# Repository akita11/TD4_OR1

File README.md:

# TD4_OR1

4bit CPU, TD4, in book ["How to Build CPU" ("CPUの創りかた" in Japanese)](https://www.amazon.co.jp/dp/4839909865/) using NDA-free PDK, [OpenRule1um](https://github.com/akita11/OpenRule1um).

## Contents

- Layout GDS: TD4core.GDS (open with [KLayout](https://www.klayout.de/), with [OpenRul1um PDK(https://github.com/MakeLSI/OpenRule1um) and [its standard cells](https://github.com/MakeLSI/OpenRule1um_StdCell) installed)

- Schematic: sch/TD4core.kicad_sch (open with EEschema in [KiCAD](https://www.kicad.org/))

## How to do LVS check

- Export netlit from TD4core.kicad_sch using EEschema, TD4core.cir.
- Add ".inc OR1SC.cir" at 2nd line in netlist file, TD4core.cir.
- Open TD4core.GDS with KLayout, execute "get_reference" macro with specifying TD4core.cir for reference netlist, and then, execute LVS (mainly digitl script).

## How to fabricate chip

- convert to fabrication GDS, with required information in fab's PDK, such as layer definitions, contact/via size conversion. Popular CMOS 0.6um PDK will satisfy OpenRule1um's design rule.

## Author

Junichi Akita (akita@fdi.jp), @akita11

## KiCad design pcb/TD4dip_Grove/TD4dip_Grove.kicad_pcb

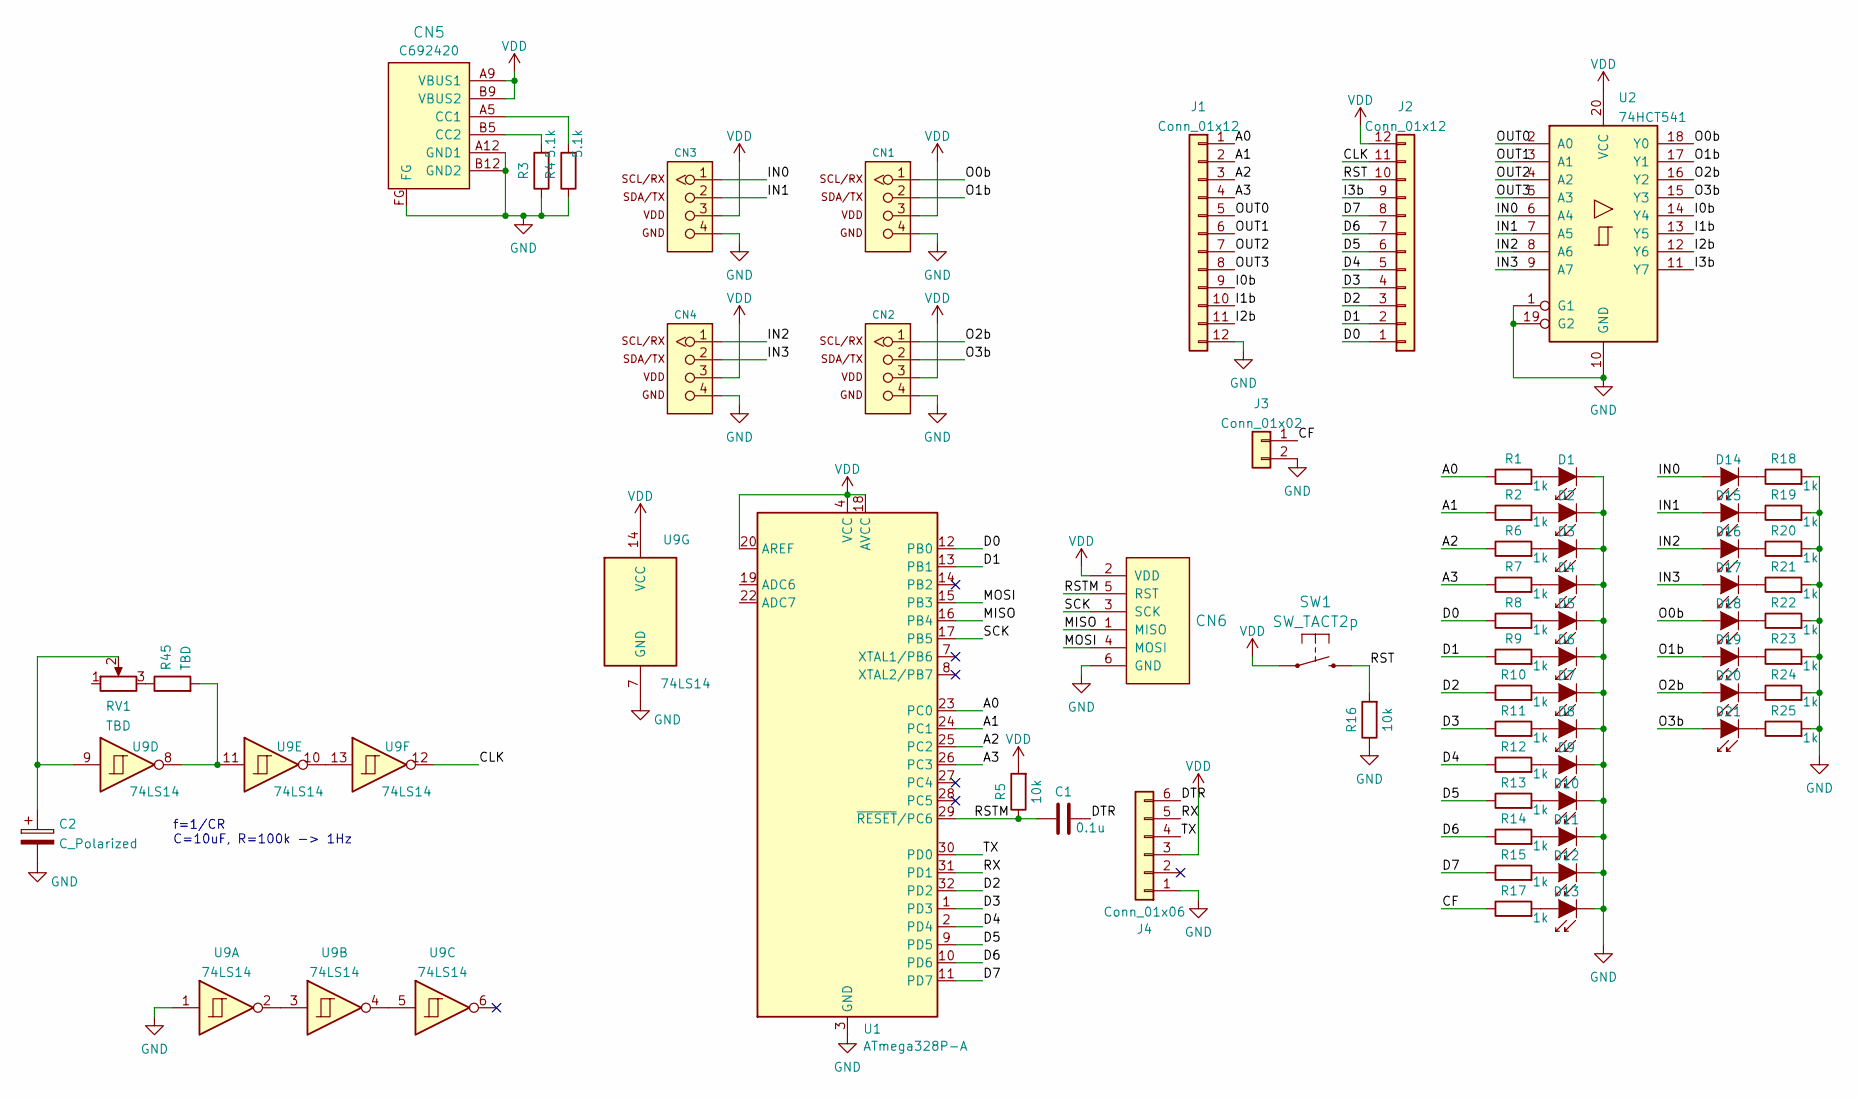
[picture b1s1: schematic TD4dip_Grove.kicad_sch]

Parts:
C1: 0.1u; C_0603_1608Metric
C2: C_Polarized; CP_Radial_D6.3mm_P2.50mm
CN1, CN2, CN3, CN4: CON_GROVE; CON_GROVE_H_roundPad
CN5: CON_USB-C-6; USB-C_6P; LCSC C692420
CN6: CON_AVRISP; PinSocket_2x03_P2.54mm_Vertical
D1, D2, D3, D4, D5, D6, D7, D8, D9, D10, D11, D12, D13, D14, D15, D16, D17, D18, D19, D20, D21: LED; LED_0603_1608Metric
J1, J2: Conn_01x12; PinSocket_1x12_P2.54mm_Vertical
J3: Conn_01x02; PinSocket_1x02_P2.54mm_Vertical
J4: Conn_01x06; PinHeader_1x06_P2.54mm_Horizontal
R1, R2, R6, R7, R8, R9, R10, R11, R12, R13, R14, R15, R17, R18, R19, R20, R21, R22, R23, R24, R25: 1k; R_0603_1608Metric
R3, R4: 5.1k; R_0603_1608Metric
R5, R16: 10k; R_0603_1608Metric
R45: TBD; R_0603_1608Metric
RV1: TBD; VR_POT_VR
SW1: SW_TACT2p; SW_Push_SPST_NO_Alps_SKRK
U1: ATmega328P-A; TQFP-32_7x7mm_P0.8mm
U2: 74HCT541; SSOP-20_4.4x6.5mm_P0.65mm
U9: 74LS14; SO-14_3.9x8.65mm_P1.27mm

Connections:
/A0: J1.1, R1.1, U1.23 (PC0)
/A1: J1.2, R2.1, U1.24 (PC1)
/A2: J1.3, R6.1, U1.25 (PC2)
/A3: J1.4, R7.1, U1.26 (PC3)
/CF: J3.1, R17.1
/CLK: J2.11, U9.12
/D0: J2.1, R8.1, U1.12 (PB0)
/D1: J2.2, R9.1, U1.13 (PB1)
/D2: J2.3, R10.1, U1.32 (PD2)
/D3: J2.4, R11.1, U1.1 (PD3)
/D4: J2.5, R12.1, U1.2 (PD4)
/D5: J2.6, R13.1, U1.9 (PD5)
/D6: J2.7, R14.1, U1.10 (PD6)
/D7: J2.8, R15.1, U1.11 (PD7)
/DTR: C1.2, J4.6
/I0b: J1.9, U2.14 (Y4)
/I1b: J1.10, U2.13 (Y5)
/I2b: J1.11, U2.12 (Y6)
/I3b: J2.9, U2.11 (Y7)
/IN0: CN3.1, D14.2 (A), U2.6 (A4)
/IN1: CN3.2, D15.2 (A), U2.7 (A5)
/IN2: CN4.1, D16.2 (A), U2.8 (A6)
/IN3: CN4.2, D17.2 (A), U2.9 (A7)
/MISO: CN6.1 (MISO), U1.16 (PB4)
/MOSI: CN6.4 (MOSI), U1.15 (PB3)
/O0b: CN1.1, D18.2 (A), U2.18 (Y0)
/O1b: CN1.2, D19.2 (A), U2.17 (Y1)
/O2b: CN2.1, D20.2 (A), U2.16 (Y2)
/O3b: CN2.2, D21.2 (A), U2.15 (Y3)
/OUT0: J1.5, U2.2 (A0)
/OUT1: J1.6, U2.3 (A1)
/OUT2: J1.7, U2.4 (A2)
/OUT3: J1.8, U2.5 (A3)
/RST: J2.10, R16.2, SW1.2
/RSTM: C1.1, CN6.5 (RST), R5.1, U1.29 (~RESET/PC6)
/RX: J4.5, U1.31 (PD1)
/SCK: CN6.3 (SCK), U1.17 (PB5)
/TX: J4.4, U1.30 (PD0)
GND: C2.2, CN1.4, CN2.4, CN3.4, CN4.4, CN5.A12 (GND1), CN5.B12 (GND2), CN5.FG, CN6.6 (GND), D1.1 (K), D2.1 (K), D3.1 (K), D4.1 (K), D5.1 (K), D6.1 (K), D7.1 (K), D8.1 (K), D9.1 (K), D10.1 (K), D11.1 (K), D12.1 (K), D13.1 (K), J1.12, J3.2, J4.1, R3.1, R4.1, R16.1, R18.2, R19.2, R20.2, R21.2, R22.2, R23.2, R24.2, R25.2, U1.3 (GND), U1.5 (GND), U1.21 (GND), U2.1 (G1), U2.10 (GND), U2.19 (G2), U9.1, U9.7 (GND)
unnamed: C2.1, RV1.2, U9.9
unnamed: CN5.A5 (CC1), R4.2
unnamed: CN5.B5 (CC2), R3.2
unnamed: D1.2 (A), R1.2
unnamed: D2.2 (A), R2.2
unnamed: D3.2 (A), R6.2
unnamed: D4.2 (A), R7.2
unnamed: D5.2 (A), R8.2
unnamed: D6.2 (A), R9.2
unnamed: D7.2 (A), R10.2
unnamed: D8.2 (A), R11.2
unnamed: D9.2 (A), R12.2
unnamed: D10.2 (A), R13.2
unnamed: D11.2 (A), R14.2
unnamed: D12.2 (A), R15.2
unnamed: D13.2 (A), R17.2
unnamed: D14.1 (K), R18.1
unnamed: D15.1 (K), R19.1
unnamed: D16.1 (K), R20.1
unnamed: D17.1 (K), R21.1
unnamed: D18.1 (K), R22.1
unnamed: D19.1 (K), R23.1
unnamed: D20.1 (K), R24.1
unnamed: D21.1 (K), R25.1
unnamed: R45.1, RV1.3
unnamed: R45.2, U9.8, U9.11
unnamed: U9.2, U9.3
unnamed: U9.4, U9.5
unnamed: U9.10, U9.13
VDD: CN1.3, CN2.3, CN3.3, CN4.3, CN5.A9 (VBUS1), CN5.B9 (VBUS2), CN6.2 (VDD), J2.12, J4.3, R5.2, SW1.1, U1.4 (VCC), U1.6 (VCC), U1.18 (AVCC), U1.20 (AREF), U2.20 (VCC), U9.14 (VCC)

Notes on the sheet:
f=1/CR C=10uF, R=100k -> 1Hz

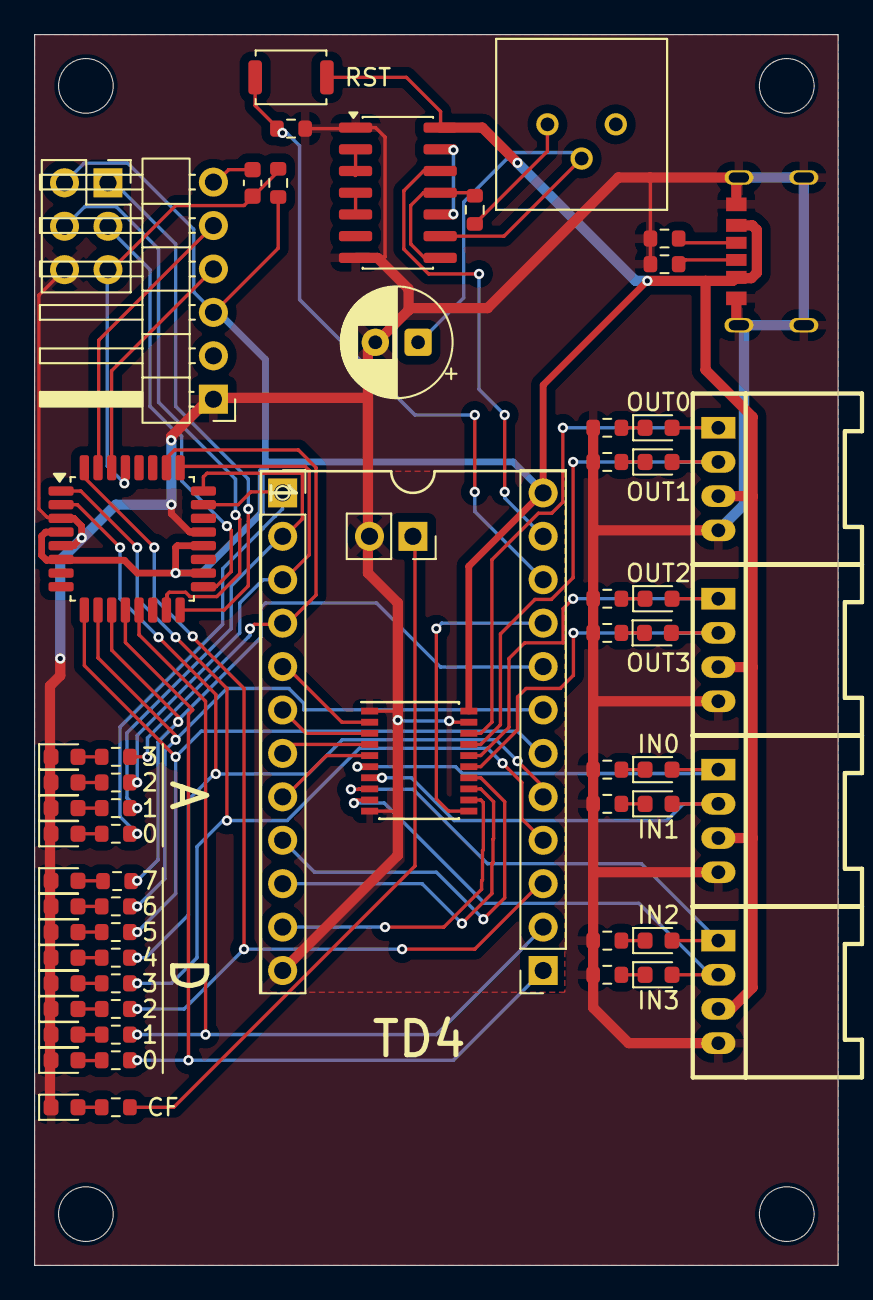
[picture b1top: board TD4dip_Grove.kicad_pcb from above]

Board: 2 copper layers, 47.0 x 72.0 mm, 64 parts (0 on the bottom side), 69 nets.

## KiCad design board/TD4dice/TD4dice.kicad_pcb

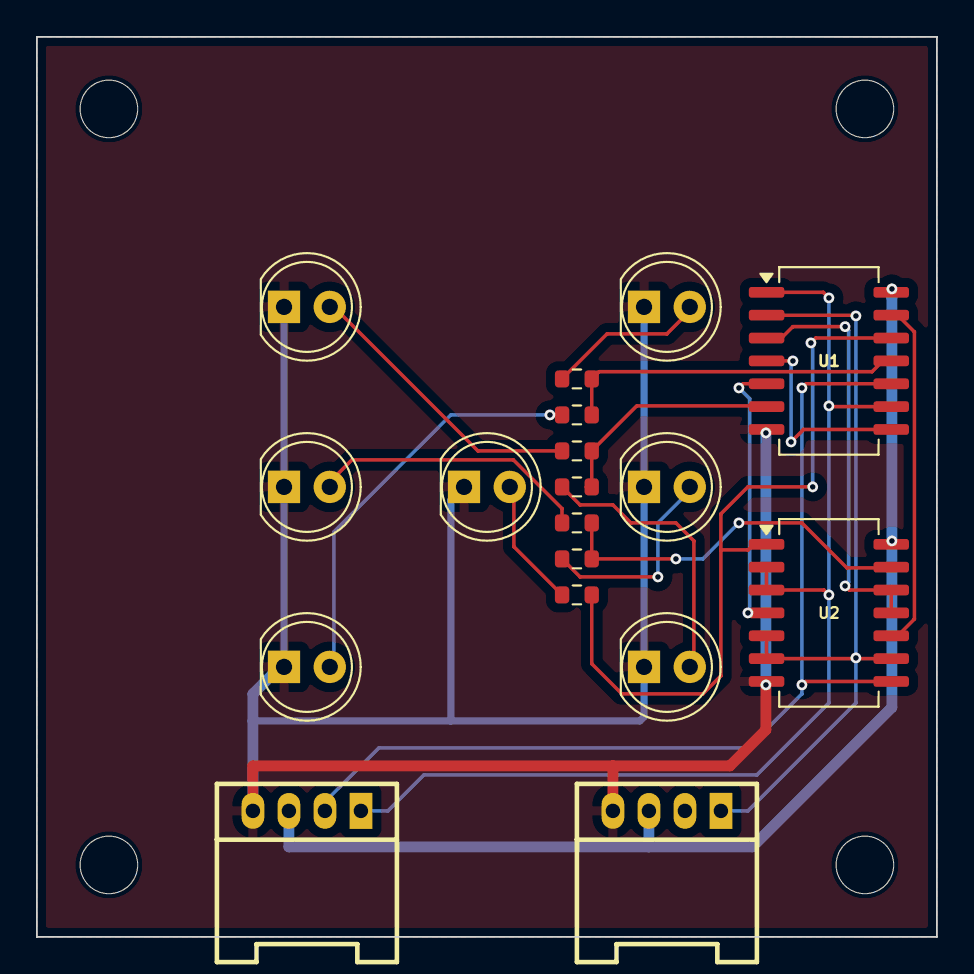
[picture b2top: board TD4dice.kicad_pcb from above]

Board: 2 copper layers, 50.0 x 50.0 mm, 18 parts (0 on the bottom side), 20 nets.

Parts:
CN1, CN2: CON_GROVE; CON_GROVE_H_roundPad
D1, D2, D3, D4, D5, D6, D7: LED; LED_D5.0mm
R1, R2, R3, R4, R5, R6, R7: 1k; R_0603_1608Metric
U1: 74HC00; SO-14_5.3x10.2mm_P1.27mm
U2: 7402; SO-14_5.3x10.2mm_P1.27mm

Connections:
+5V: CN1.3, CN2.3, U1.14 (VCC), U2.14 (VCC)
/A: CN1.1, U1.1, U1.9, U2.2, U2.3
/B: CN1.2, U1.10, U2.8
/C: CN2.1, U1.2, U2.5, U2.6, U2.9
/LEDAF: R1.1, R6.1, U1.6
/LEDBE: R2.1, R5.1, U1.11
/LEDCD: R3.1, R4.1, U2.13
/LEDG: R7.1, U1.12, U2.1
GND: CN1.4, CN2.4, D1.1 (K), D2.1 (K), D3.1 (K), D4.1 (K), D5.1 (K), D6.1 (K), D7.1 (K), U1.7 (GND), U2.7 (GND)
unnamed: D1.2 (A), R1.2
unnamed: D2.2 (A), R2.2
unnamed: D3.2 (A), R3.2
unnamed: D4.2 (A), R4.2
unnamed: D5.2 (A), R5.2
unnamed: D6.2 (A), R6.2
unnamed: D7.2 (A), R7.2
unnamed: U1.3, U2.11, U2.12
unnamed: U1.4, U1.8
unnamed: U1.5, U2.4
unnamed: U1.13, U2.10

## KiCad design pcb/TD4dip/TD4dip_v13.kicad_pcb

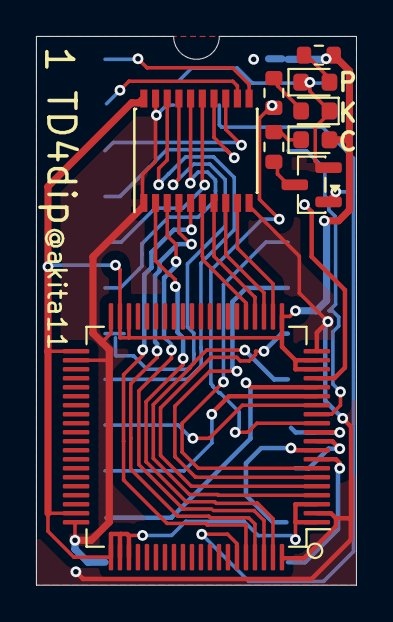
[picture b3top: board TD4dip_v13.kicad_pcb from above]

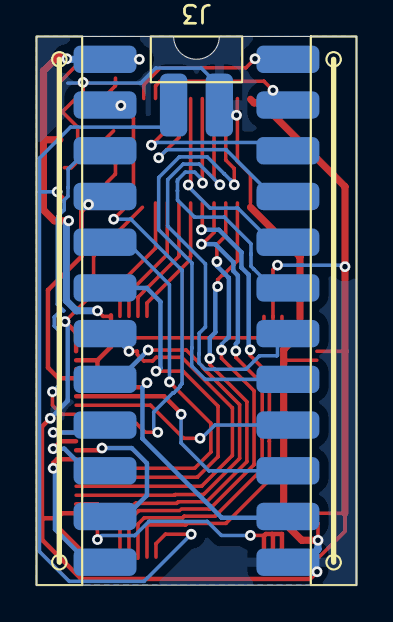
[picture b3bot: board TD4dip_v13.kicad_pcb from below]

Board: 2 copper layers, 17.8 x 30.5 mm, 12 parts (3 on the bottom side), 37 nets.

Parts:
D1, D2, D3: LED; LED_0603_1608Metric
J1, J2: Conn_01x12; CON_12pL_SMD
J3: Conn_01x02; CON_2pL_SMD
Q1: TR_NMOS_IRLML6344; SOT-23
R1, R2, R3: 1k; R_0603_1608Metric
U1: IC80p; LQFP-80_12x12mm_P0.5mm
U2: 74HCT541; SSOP-20_4.4x6.5mm_P0.65mm

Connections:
/A0: U1.22, U2.9 (A7)
/A0b: J1.1, U2.11 (Y7)
/A1: U1.23, U2.8 (A6)
/A1b: J1.2, U2.12 (Y6)
/A2: U1.24, U2.7 (A5)
/A2b: J1.3, U2.13 (Y5)
/A3: U1.25, U2.6 (A4)
/A3b: J1.4, U2.14 (Y4)
/CF: J3.1, Q1.1 (G), U1.75
/CLK: J2.11, R2.1, U1.12
/D0: J2.1, U1.8
/D1: J2.2, U1.9
/D2: J2.3, U1.10
/D3: J2.4, U1.11
/D4: J2.5, U1.4
/D5: J2.6, U1.5
/D6: J2.7, U1.6
/D7: J2.8, U1.7
/IN0: J1.9, U1.14
/IN1: J1.10, U1.15
/IN2: J1.11, U1.16
/IN3: J2.9, U1.17
/O0b: J1.5, U2.15 (Y3)
/O1b: J1.6, U2.16 (Y2)
/O2b: J1.7, U2.17 (Y1)
/O3b: J1.8, U2.18 (Y0)
/OUT0: U1.76, U2.5 (A3)
/OUT1: U1.77, U2.4 (A2)
/OUT2: U1.78, U2.3 (A1)
/OUT3: U1.79, U2.2 (A0)
/RST: J2.10, U1.13
GND: D1.1 (K), D2.1 (K), J1.12, J3.2, Q1.2 (S), U1.2, U1.20, U1.40, U1.42, U1.60, U1.80, U2.1 (G1), U2.10 (GND), U2.19 (G2)
unnamed: D1.2 (A), R1.2
unnamed: D2.2 (A), R2.2
unnamed: D3.1 (K), R3.2
unnamed: Q1.3 (D), R3.1
VDD: D3.2 (A), J2.12, R1.1, U1.1, U1.3, U1.18, U1.19, U1.21, U1.38, U1.39, U1.41, U1.59, U1.61, U1.62, U1.63, U2.20 (VCC)

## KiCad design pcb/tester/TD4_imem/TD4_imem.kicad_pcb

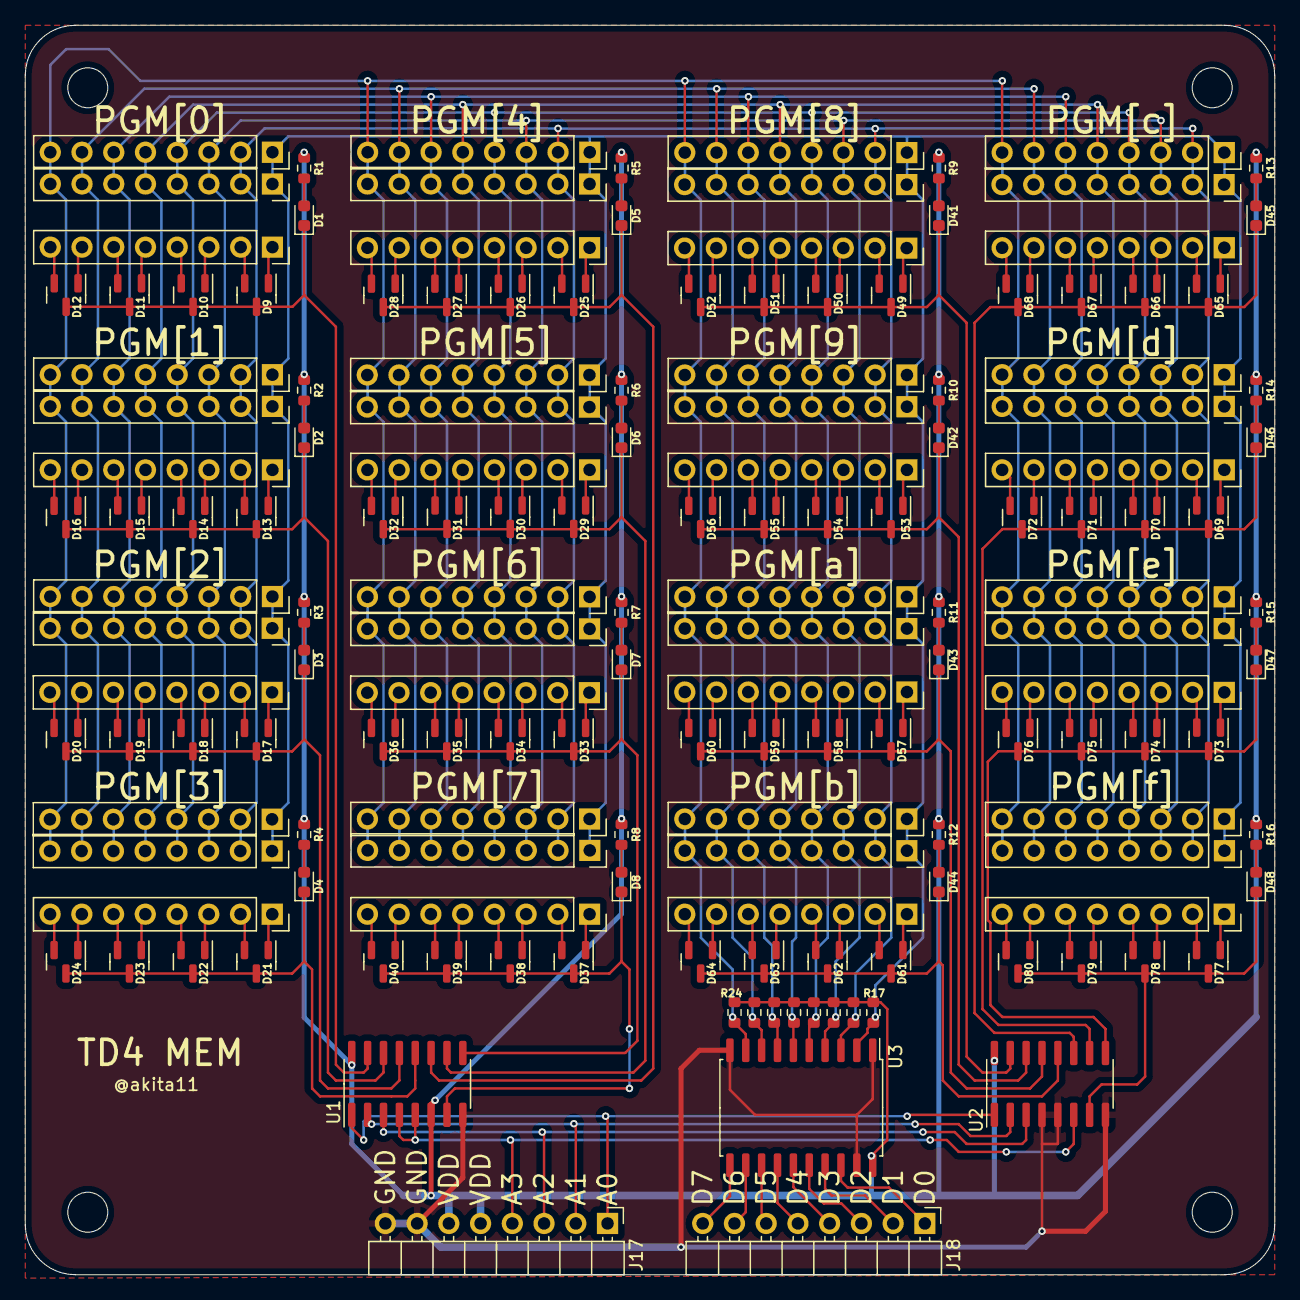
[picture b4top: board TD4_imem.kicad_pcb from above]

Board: 2 copper layers, 100.0 x 100.0 mm, 157 parts (0 on the bottom side), 182 nets.

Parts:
D1, D2, D3, D4, D5, D6, D7, D8, D41, D42, D43, D44, D45, D46, D47, D48: LED; LED_0603_1608Metric
D9, D10, D11, D12, D13, D14, D15, D16, D17, D18, D19, D20, D21, D22, D23, D24, D25, D26, D27, D28, D29, D30, D31, D32, D33, D34, D35, D36, D37, D38, D39, D40, D49, D50, D51, D52, D53, D54, D55, D56, D57, D58, D59, D60, D61, D62, D63, D64, D65, D66, D67, D68, D69, D70, D71, D72, D73, D74, D75, D76, D77, D78, D79, D80: BAT54C; SOT-23
J1, J2, J3, J4, J5, J6, J7, J8, J9, J10, J11, J12, J13, J14, J15, J16, J101, J102, J103, J104, J105, J106, J107, J108, J109, J110, J111, J112, J113, J114, J115, J116, J201, J202, J203, J204, J205, J206, J207, J208, J209, J210, J211, J212, J213, J214, J215, J216: Conn_01x08; PinSocket_1x08_P2.54mm_Vertical
J17, J18: Conn_01x08; PinHeader_1x08_P2.54mm_Horizontal
R1, R2, R3, R4, R5, R6, R7, R8, R9, R10, R11, R12, R13, R14, R15, R16: 1k; R_0603_1608Metric
R17, R18, R19, R20, R21, R22, R23, R24: 10k; R_0603_1608Metric
U1, U2: 74LS138; SOIC-16_3.9x9.9mm_P1.27mm
U3: 74LS540; SOP-20_7.5x12.8mm_P1.27mm

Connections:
/A0: J17.1, U1.1 (A0), U2.1 (A0)
/A1: J17.2, U1.2 (A1), U2.2 (A1)
/A2: J17.3, U1.3 (A2), U2.3 (A2)
/A3: J17.4, U1.4 (E1), U1.5 (E2), U2.6 (E3)
/D0: J1.1, J2.1, J3.1, J4.1, J5.1, J6.1, J7.1, J8.1, J9.1, J10.1, J11.1, J12.1, J13.1, J14.1, J15.1, J16.1, J101.1, J102.1, J103.1, J104.1, J105.1, J106.1, J107.1, J108.1, J109.1, J110.1, J111.1, J112.1, J113.1, J114.1, J115.1, J116.1, R17.2, U3.2 (A0)
/D1: J1.2, J2.2, J3.2, J4.2, J5.2, J6.2, J7.2, J8.2, J9.2, J10.2, J11.2, J12.2, J13.2, J14.2, J15.2, J16.2, J101.2, J102.2, J103.2, J104.2, J105.2, J106.2, J107.2, J108.2, J109.2, J110.2, J111.2, J112.2, J113.2, J114.2, J115.2, J116.2, R18.2, U3.3 (A1)
/D2: J1.3, J2.3, J3.3, J4.3, J5.3, J6.3, J7.3, J8.3, J9.3, J10.3, J11.3, J12.3, J13.3, J14.3, J15.3, J16.3, J101.3, J102.3, J103.3, J104.3, J105.3, J106.3, J107.3, J108.3, J109.3, J110.3, J111.3, J112.3, J113.3, J114.3, J115.3, J116.3, R19.2, U3.4 (A2)
/D3: J1.4, J2.4, J3.4, J4.4, J5.4, J6.4, J7.4, J8.4, J9.4, J10.4, J11.4, J12.4, J13.4, J14.4, J15.4, J16.4, J101.4, J102.4, J103.4, J104.4, J105.4, J106.4, J107.4, J108.4, J109.4, J110.4, J111.4, J112.4, J113.4, J114.4, J115.4, J116.4, R20.2, U3.5 (A3)
/D4: J1.5, J2.5, J3.5, J4.5, J5.5, J6.5, J7.5, J8.5, J9.5, J10.5, J11.5, J12.5, J13.5, J14.5, J15.5, J16.5, J101.5, J102.5, J103.5, J104.5, J105.5, J106.5, J107.5, J108.5, J109.5, J110.5, J111.5, J112.5, J113.5, J114.5, J115.5, J116.5, R21.2, U3.6 (A4)
/D5: J1.6, J2.6, J3.6, J4.6, J5.6, J6.6, J7.6, J8.6, J9.6, J10.6, J11.6, J12.6, J13.6, J14.6, J15.6, J16.6, J101.6, J102.6, J103.6, J104.6, J105.6, J106.6, J107.6, J108.6, J109.6, J110.6, J111.6, J112.6, J113.6, J114.6, J115.6, J116.6, R22.2, U3.7 (A5)
/D6: J1.7, J2.7, J3.7, J4.7, J5.7, J6.7, J7.7, J8.7, J9.7, J10.7, J11.7, J12.7, J13.7, J14.7, J15.7, J16.7, J101.7, J102.7, J103.7, J104.7, J105.7, J106.7, J107.7, J108.7, J109.7, J110.7, J111.7, J112.7, J113.7, J114.7, J115.7, J116.7, R23.2, U3.8 (A6)
/D7: J1.8, J2.8, J3.8, J4.8, J5.8, J6.8, J7.8, J8.8, J9.8, J10.8, J11.8, J12.8, J13.8, J14.8, J15.8, J16.8, J101.8, J102.8, J103.8, J104.8, J105.8, J106.8, J107.8, J108.8, J109.8, J110.8, J111.8, J112.8, J113.8, J114.8, J115.8, J116.8, R24.2, U3.9 (A7)
/DB0: J18.1, U3.18 (Y0)
/DB1: J18.2, U3.17 (Y1)
/DB2: J18.3, U3.16 (Y2)
/DB3: J18.4, U3.15 (Y3)
/DB4: J18.5, U3.14 (Y4)
/DB5: J18.6, U3.13 (Y5)
/DB6: J18.7, U3.12 (Y6)
/DB7: J18.8, U3.11 (Y7)
GND: J17.7, J17.8, U1.8 (GND), U2.4 (E1), U2.5 (E2), U2.8 (GND), U3.1 (G1), U3.10 (GND), U3.19 (G2)
unnamed: D1.1 (K), D9.3, D10.3, D11.3, D12.3, U1.15 (O0)
unnamed: D1.2 (A), R1.2
unnamed: D2.2 (A), R2.2
unnamed: D3.2 (A), R3.2
unnamed: D4.2 (A), R4.2
unnamed: D5.2 (A), R5.2
unnamed: D6.2 (A), R6.2
unnamed: D7.2 (A), R7.2
unnamed: D8.2 (A), R8.2
unnamed: D9.1, J201.1
unnamed: D9.2, J201.2
unnamed: D10.1, J201.3
unnamed: D10.2, J201.4
unnamed: D11.1, J201.5
unnamed: D11.2, J201.6
unnamed: D12.1, J201.7
unnamed: D12.2, J201.8
unnamed: D13.1, J202.1
unnamed: D13.2, J202.2
unnamed: D2.1 (K), D13.3, D14.3, D15.3, D16.3, U1.14 (O1)
unnamed: D14.1, J202.3
unnamed: D14.2, J202.4
unnamed: D15.1, J202.5
unnamed: D15.2, J202.6
unnamed: D16.1, J202.7
unnamed: D16.2, J202.8
unnamed: D17.1, J203.1
unnamed: D17.2, J203.2
unnamed: D3.1 (K), D17.3, D18.3, D19.3, D20.3, U1.13 (O2)
unnamed: D18.1, J203.3
unnamed: D18.2, J203.4
unnamed: D19.1, J203.5
unnamed: D19.2, J203.6
unnamed: D20.1, J203.7
unnamed: D20.2, J203.8
unnamed: D21.1, J204.1
unnamed: D21.2, J204.2
unnamed: D4.1 (K), D21.3, D22.3, D23.3, D24.3, U1.12 (O3)
unnamed: D22.1, J204.3
unnamed: D22.2, J204.4
unnamed: D23.1, J204.5
unnamed: D23.2, J204.6
unnamed: D24.1, J204.7
unnamed: D24.2, J204.8
unnamed: D25.1, J205.1
unnamed: D25.2, J205.2
unnamed: D5.1 (K), D25.3, D26.3, D27.3, D28.3, U1.11 (O4)
unnamed: D26.1, J205.3
unnamed: D26.2, J205.4
unnamed: D27.1, J205.5
unnamed: D27.2, J205.6
unnamed: D28.1, J205.7
unnamed: D28.2, J205.8
unnamed: D29.1, J206.1
unnamed: D29.2, J206.2
unnamed: D6.1 (K), D29.3, D30.3, D31.3, D32.3, U1.10 (O5)
unnamed: D30.1, J206.3
unnamed: D30.2, J206.4
unnamed: D31.1, J206.5
unnamed: D31.2, J206.6
unnamed: D32.1, J206.7
unnamed: D32.2, J206.8
unnamed: D33.1, J207.1
unnamed: D33.2, J207.2
unnamed: D7.1 (K), D33.3, D34.3, D35.3, D36.3, U1.9 (O6)
unnamed: D34.1, J207.3
unnamed: D34.2, J207.4
unnamed: D35.1, J207.5
unnamed: D35.2, J207.6
unnamed: D36.1, J207.7
unnamed: D36.2, J207.8
unnamed: D37.1, J208.1
unnamed: D37.2, J208.2
unnamed: D8.1 (K), D37.3, D38.3, D39.3, D40.3, U1.7 (O7)
unnamed: D38.1, J208.3
unnamed: D38.2, J208.4
unnamed: D39.1, J208.5
unnamed: D39.2, J208.6
unnamed: D40.1, J208.7
unnamed: D40.2, J208.8
unnamed: D41.1 (K), D49.3, D50.3, D51.3, D52.3, U2.15 (O0)
unnamed: D41.2 (A), R9.2
unnamed: D42.1 (K), D53.3, D54.3, D55.3, D56.3, U2.14 (O1)
unnamed: D42.2 (A), R10.2
unnamed: D43.1 (K), D57.3, D58.3, D59.3, D60.3, U2.13 (O2)
unnamed: D43.2 (A), R11.2
unnamed: D44.1 (K), D61.3, D62.3, D63.3, D64.3, U2.12 (O3)
unnamed: D44.2 (A), R12.2
unnamed: D45.1 (K), D65.3, D66.3, D67.3, D68.3, U2.11 (O4)
unnamed: D45.2 (A), R13.2
unnamed: D46.1 (K), D69.3, D70.3, D71.3, D72.3, U2.10 (O5)
unnamed: D46.2 (A), R14.2
unnamed: D47.1 (K), D73.3, D74.3, D75.3, D76.3, U2.9 (O6)
unnamed: D47.2 (A), R15.2
unnamed: D48.1 (K), D77.3, D78.3, D79.3, D80.3, U2.7 (O7)
unnamed: D48.2 (A), R16.2
unnamed: D49.1, J209.1
unnamed: D49.2, J209.2
unnamed: D50.1, J209.3
unnamed: D50.2, J209.4
unnamed: D51.1, J209.5
unnamed: D51.2, J209.6
unnamed: D52.1, J209.7
unnamed: D52.2, J209.8
unnamed: D53.1, J210.1
unnamed: D53.2, J210.2
unnamed: D54.1, J210.3
unnamed: D54.2, J210.4
unnamed: D55.1, J210.5
unnamed: D55.2, J210.6
unnamed: D56.1, J210.7
unnamed: D56.2, J210.8
unnamed: D57.1, J211.1
unnamed: D57.2, J211.2
unnamed: D58.1, J211.3
unnamed: D58.2, J211.4
unnamed: D59.1, J211.5
unnamed: D59.2, J211.6
unnamed: D60.1, J211.7
unnamed: D60.2, J211.8
unnamed: D61.1, J212.1
unnamed: D61.2, J212.2
unnamed: D62.1, J212.3
unnamed: D62.2, J212.4
unnamed: D63.1, J212.5
unnamed: D63.2, J212.6
unnamed: D64.1, J212.7
unnamed: D64.2, J212.8
unnamed: D65.1, J213.1
unnamed: D65.2, J213.2
unnamed: D66.1, J213.3
unnamed: D66.2, J213.4
unnamed: D67.1, J213.5
unnamed: D67.2, J213.6
unnamed: D68.1, J213.7
unnamed: D68.2, J213.8
unnamed: D69.1, J214.1
unnamed: D69.2, J214.2
unnamed: D70.1, J214.3
unnamed: D70.2, J214.4
unnamed: D71.1, J214.5
unnamed: D71.2, J214.6
unnamed: D72.1, J214.7
unnamed: D72.2, J214.8
unnamed: D73.1, J215.1
unnamed: D73.2, J215.2
unnamed: D74.1, J215.3
unnamed: D74.2, J215.4
unnamed: D75.1, J215.5
unnamed: D75.2, J215.6
unnamed: D76.1, J215.7
unnamed: D76.2, J215.8
unnamed: D77.1, J216.1
unnamed: D77.2, J216.2
unnamed: D78.1, J216.3
unnamed: D78.2, J216.4
unnamed: D79.1, J216.5
unnamed: D79.2, J216.6
unnamed: D80.1, J216.7
unnamed: D80.2, J216.8
VDD: J17.5, J17.6, R1.1, R2.1, R3.1, R4.1, R5.1, R6.1, R7.1, R8.1, R9.1, R10.1, R11.1, R12.1, R13.1, R14.1, R15.1, R16.1, R17.1, R18.1, R19.1, R20.1, R21.1, R22.1, R23.1, R24.1, U1.6 (E3), U1.16 (VCC), U2.16 (VCC), U3.20 (VCC)

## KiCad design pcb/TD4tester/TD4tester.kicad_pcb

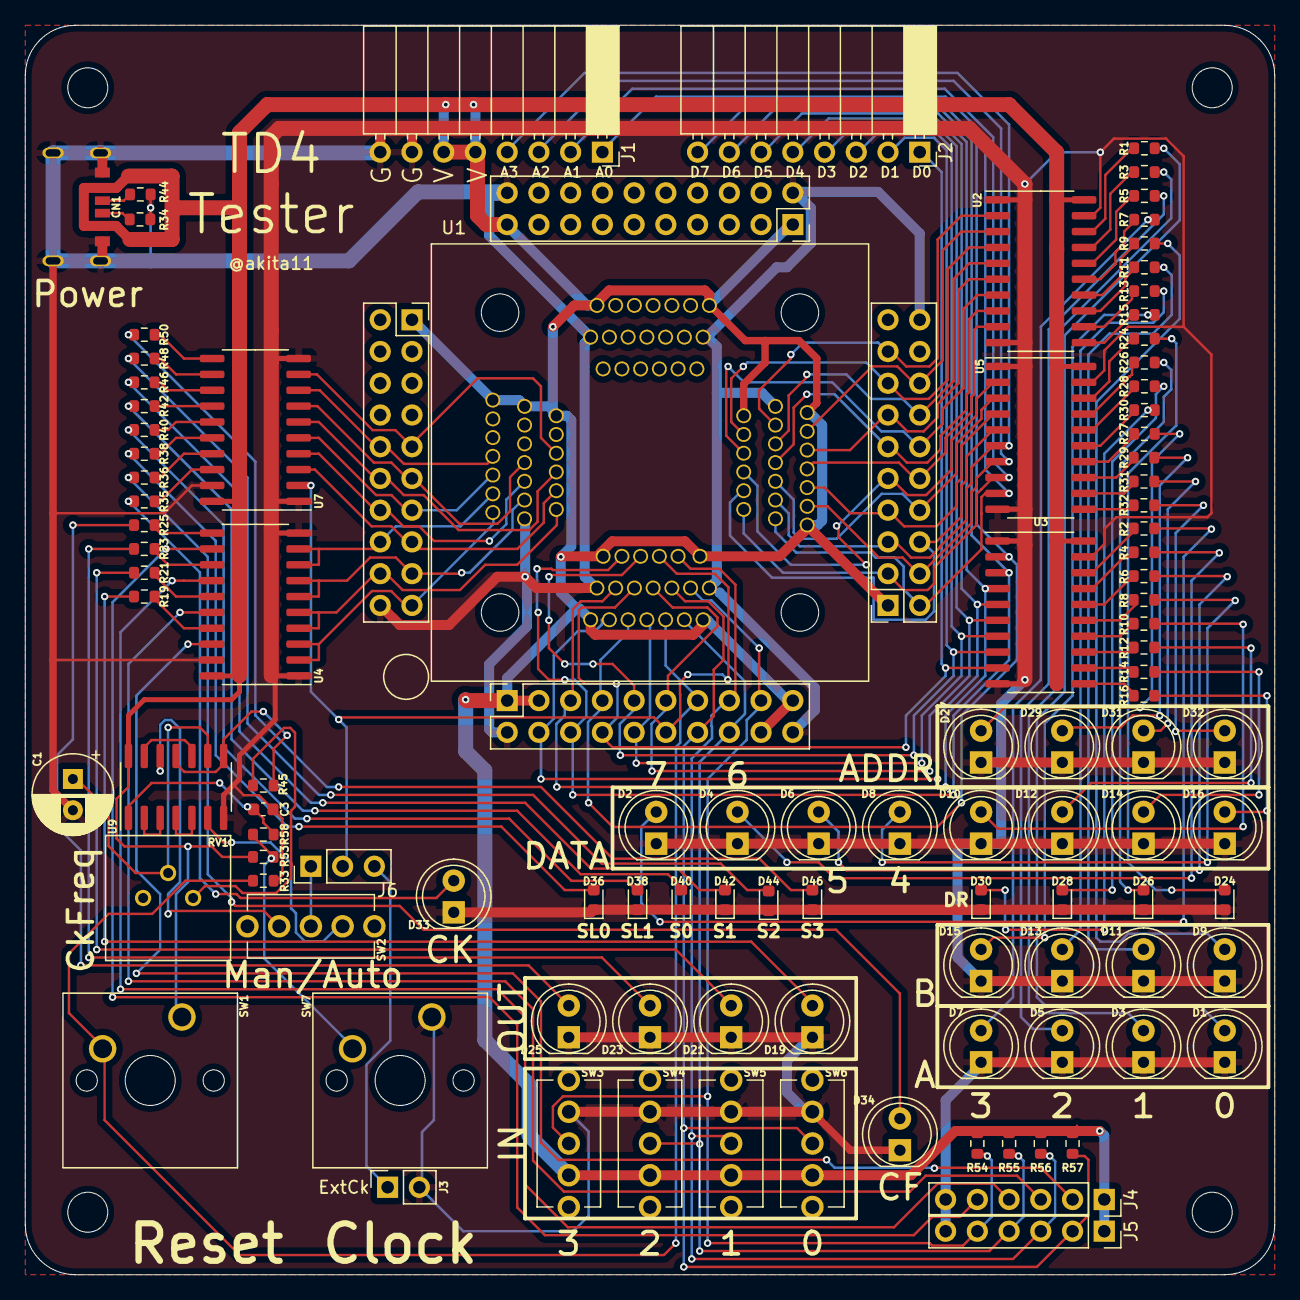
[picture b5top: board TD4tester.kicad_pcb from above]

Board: 2 copper layers, 100.0 x 100.0 mm, 110 parts (0 on the bottom side), 133 nets.

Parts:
C1: C_Polarized; CP_Radial_D6.3mm_P2.50mm
C3: C; C_0603_1608Metric
CN1: CON_USB-C-6; USB-C_6P
D1, D2, D3, D4, D5, D6, D7, D8, D9, D10, D11, D12, D13, D14, D15, D16, D19, D21, D23, D25, D27, D29, D31, D32, D33, D34: LED; LED_D5.0mm
D24, D26, D28, D30, D36, D38, D40, D42, D44, D46: LED; LED_0603_1608Metric
J1, J2: Conn_01x08; PinSocket_1x08_P2.54mm_Horizontal
J3: Conn_01x02; PinSocket_1x02_P2.54mm_Vertical
J4, J5: Conn_01x06; PinSocket_1x06_P2.54mm_Vertical
J6: Conn_01x03; PinHeader_1x03_P2.54mm_Vertical
J7, J8, J9, J10: Conn_02x10_Odd_Even; PinSocket_2x10_P2.54mm_Vertical
R1, R2, R3, R4, R5, R6, R7, R8, R9, R10, R11, R12, R13, R14, R15, R16, R19, R21, R23, R24, R25, R26, R27, R28, R29, R30, R31, R32, R35, R36, R38, R40, R42, R46, R48, R50: 1k; R_0603_1608Metric
R33, R53, R54, R55, R56, R57, R58: 10k; R_0603_1608Metric
R34, R44: 5.1k; R_0603_1608Metric
R45: TBD; R_0603_1608Metric
RV1: TBD; VR_POT_VR
SW1, SW7: SW_Push; SW_Cherry_MX_1.00u_PCB
SW2, SW3, SW4, SW5, SW6: SW_SPDT; SW_SPDT_Frame
U1: IC80p; SOCKET_IC51-0804-808
U2, U3, U4, U5, U7: 74LS541; SO-20_5.3x12.6mm_P1.27mm
U9: 74LS14; SO-14_3.9x8.65mm_P1.27mm

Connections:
/A0: J1.1, J8.2, U1.22, U5.9 (A7)
/A1: J1.2, J8.3, U1.23, U5.8 (A6)
/A2: J1.3, J8.4, U1.24, U5.7 (A5)
/A3: J1.4, J8.5, U1.25, U5.6 (A4)
/CF: J10.15, U1.75, U7.3 (A1)
/CK: J6.2, J7.12, U1.12, U7.2 (A0)
/CKe: J3.1, J6.3
/D0: J2.1, J7.8, U1.8, U3.9 (A7)
/D1: J2.2, J7.9, U1.9, U3.8 (A6)
/D2: J2.3, J7.10, U1.10, U3.7 (A5)
/D3: J2.4, J7.11, U1.11, U3.6 (A4)
/D4: J2.5, J7.4, U1.4, U3.5 (A3)
/D5: J2.6, J7.5, U1.5, U3.4 (A2)
/D6: J2.7, J7.6, U1.6, U3.3 (A1)
/D7: J2.8, J7.7, U1.7, U3.2 (A0)
/DA0: J8.17, U1.37, U2.2 (A0)
/DA1: J8.16, U1.36, U2.3 (A1)
/DA2: J8.15, U1.35, U2.4 (A2)
/DA3: J8.14, U1.34, U2.5 (A3)
/DB0: J8.13, U1.33, U2.6 (A4)
/DB1: J8.12, U1.32, U2.7 (A5)
/DB2: J8.11, U1.31, U2.8 (A6)
/DB3: J8.10, U1.30, U2.9 (A7)
/DR0: J8.9, U1.29, U5.2 (A0)
/DR1: J8.8, U1.28, U5.3 (A1)
/DR2: J8.7, U1.27, U5.4 (A2)
/DR3: J8.6, U1.26, U5.5 (A3)
/IN0: J5.2, J7.14, R57.2, SW6.2 (B), U1.14
/IN1: J5.3, J7.15, R56.2, SW5.2 (B), U1.15
/IN2: J5.4, J7.16, R55.2, SW4.2 (B), U1.16
/IN3: J5.5, J7.17, R54.2, SW3.2 (B), U1.17
/OUT0: J10.16, U1.76, U4.8 (A6), U4.9 (A7)
/OUT0e: J4.2, U4.18 (Y0)
/OUT1: J10.17, U1.77, U4.6 (A4), U4.7 (A5)
/OUT1e: J4.3, U4.16 (Y2)
/OUT2: J10.18, U1.78, U4.4 (A2), U4.5 (A3)
/OUT2e: J4.4, U4.14 (Y4)
/OUT3: J10.19, U1.79, U4.2 (A0), U4.3 (A1)
/OUT3e: J4.5, U4.12 (Y6)
/RST: J7.13, R33.1, SW1.2, U1.13
/S0: J10.12, U1.72, U7.6 (A4)
/S1: J10.11, U1.71, U7.7 (A5)
/S2: J10.10, U1.70, U7.8 (A6)
/S3: J10.9, U1.69, U7.9 (A7)
/SL0: J10.14, U1.74, U7.4 (A2)
/SL1: J10.13, U1.73, U7.5 (A3)
GND: C1.2, C3.2, CN1.A12 (GND1), CN1.B12 (GND2), CN1.FG, D1.1 (K), D2.1 (K), D3.1 (K), D4.1 (K), D5.1 (K), D6.1 (K), D7.1 (K), D8.1 (K), D9.1 (K), D10.1 (K), D11.1 (K), D12.1 (K), D13.1 (K), D14.1 (K), D15.1 (K), D16.1 (K), D19.1 (K), D21.1 (K), D23.1 (K), D24.1 (K), D25.1 (K), D26.1 (K), D27.1 (K), D28.1 (K), D29.1 (K), D30.1 (K), D31.1 (K), D32.1 (K), D33.1 (K), D34.1 (K), D36.1 (K), D38.1 (K), D40.1 (K), D42.1 (K), D44.1 (K), D46.1 (K), J1.7, J1.8, J3.2, J4.6, J5.6, J7.2, J7.20, J8.20, J9.2, J9.20, J10.20, R33.2, R34.1, R44.1, SW3.3 (C), SW4.3 (C), SW5.3 (C), SW6.3 (C), SW7.1, U1.2, U1.20, U1.40, U1.42, U1.60, U1.80, U2.1 (G1), U2.10 (GND), U2.19 (G2), U3.1 (G1), U3.10 (GND), U3.19 (G2), U4.1 (G1), U4.10 (GND), U4.19 (G2), U5.1 (G1), U5.10 (GND), U5.19 (G2), U7.1 (G1), U7.10 (GND), U7.19 (G2), U9.7 (GND)
unnamed: C1.1, RV1.2, U9.9
unnamed: C3.1, R58.2, U9.1
unnamed: CN1.A5 (CC1), R44.2
unnamed: CN1.B5 (CC2), R34.2
unnamed: D1.2 (A), R1.2
unnamed: D2.2 (A), R2.2
unnamed: D3.2 (A), R3.2
unnamed: D4.2 (A), R4.2
unnamed: D5.2 (A), R5.2
unnamed: D6.2 (A), R6.2
unnamed: D7.2 (A), R7.2
unnamed: D8.2 (A), R8.2
unnamed: D9.2 (A), R9.2
unnamed: D10.2 (A), R10.2
unnamed: D11.2 (A), R11.2
unnamed: D12.2 (A), R12.2
unnamed: D13.2 (A), R13.2
unnamed: D14.2 (A), R14.2
unnamed: D15.2 (A), R15.2
unnamed: D16.2 (A), R16.2
unnamed: D24.2 (A), R24.2
unnamed: D25.2 (A), R25.2
unnamed: D26.2 (A), R26.2
unnamed: D27.2 (A), R27.2
unnamed: D28.2 (A), R28.2
unnamed: D29.2 (A), R29.2
unnamed: D30.2 (A), R30.2
unnamed: D31.2 (A), R31.2
unnamed: D32.2 (A), R32.2
unnamed: D33.2 (A), R35.2
unnamed: D34.2 (A), R36.2
unnamed: D36.2 (A), R38.2
unnamed: D38.2 (A), R40.2
unnamed: D40.2 (A), R42.2
unnamed: D42.2 (A), R46.2
unnamed: D44.2 (A), R48.2
unnamed: D46.2 (A), R50.2
unnamed: J6.1, SW2.2 (B)
unnamed: R1.1, U2.18 (Y0)
unnamed: R2.1, U3.18 (Y0)
unnamed: R3.1, U2.17 (Y1)
unnamed: R4.1, U3.17 (Y1)
unnamed: R5.1, U2.16 (Y2)
unnamed: R6.1, U3.16 (Y2)
unnamed: R7.1, U2.15 (Y3)
unnamed: R8.1, U3.15 (Y3)
unnamed: R9.1, U2.14 (Y4)
unnamed: R10.1, U3.14 (Y4)
unnamed: R11.1, U2.13 (Y5)
unnamed: R12.1, U3.13 (Y5)
unnamed: R13.1, U2.12 (Y6)
unnamed: R14.1, U3.12 (Y6)
unnamed: R15.1, U2.11 (Y7)
unnamed: R16.1, U3.11 (Y7)
unnamed: R19.1, U4.17 (Y1)
unnamed: D19.2 (A), R19.2
unnamed: R21.1, U4.15 (Y3)
unnamed: D21.2 (A), R21.2
unnamed: D23.2 (A), R23.2
unnamed: R24.1, U5.18 (Y0)
unnamed: R26.1, U5.17 (Y1)
unnamed: R27.1, U5.14 (Y4)
unnamed: R28.1, U5.16 (Y2)
unnamed: R29.1, U5.13 (Y5)
unnamed: R30.1, U5.15 (Y3)
unnamed: R31.1, U5.12 (Y6)
unnamed: R32.1, U5.11 (Y7)
unnamed: R35.1, U7.18 (Y0)
unnamed: R36.1, U7.17 (Y1)
unnamed: R38.1, U7.16 (Y2)
unnamed: R40.1, U7.15 (Y3)
unnamed: R42.1, U7.14 (Y4)
unnamed: R45.1, RV1.3
unnamed: R45.2, U9.8, U9.11
unnamed: R46.1, U7.13 (Y5)
unnamed: R48.1, U7.12 (Y6)
unnamed: R50.1, U7.11 (Y7)
unnamed: R53.2, R58.1, SW7.2
unnamed: SW2.1 (A), U9.6
unnamed: SW2.3 (C), U9.12
unnamed: R25.1, U4.11 (Y7)
unnamed: R23.1, U4.13 (Y5)
unnamed: U9.2, U9.3
unnamed: U9.4, U9.5
unnamed: U9.10, U9.13
VDD: CN1.A9 (VBUS1), CN1.B9 (VBUS2), J1.5, J1.6, J4.1, J5.1, J7.1, J7.3, J7.18, J7.19, J8.1, J9.1, J9.19, J10.1, R53.1, R54.1, R55.1, R56.1, R57.1, SW1.1, SW3.1 (A), SW4.1 (A), SW5.1 (A), SW6.1 (A), U1.1, U1.3, U1.18, U1.19, U1.21, U1.38, U1.39, U1.41, U1.59, U1.61, U1.62, U1.63, U2.20 (VCC), U3.20 (VCC), U4.20 (VCC), U5.20 (VCC), U7.20 (VCC), U9.14 (VCC)

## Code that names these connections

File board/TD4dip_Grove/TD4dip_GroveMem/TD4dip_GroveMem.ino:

// A: [A3:A0] (PC3:PC0)
// D: [D7:D2 + D9:D8] (PB1:PB0 + PD7:PD2)

uint8_t mem[] = {
  //0     1     2     3     4     5     6     7     8     9     a     b     c     d     e     f 
//0x00, 0x01, 0x02, 0x03, 0x04, 0x05, 0x06, 0x07, 0x08, 0x09, 0x0a, 0x0b, 0x0c, 0x0d, 0x0e, 0x0f
  // blink (count up)
  0x70, 0x90, 0x51, 0xf1, 0x00, 0x00, 0x00, 0x00, 0x00, 0x00, 0x00, 0x00, 0x00, 0x00, 0x00, 0x00 // OUT blink (MOV B,0 / OUT B / ADD B,1 / JMP 1)

void setup() {
#define ADDR_PINMODE INPUT
//#define ADDR_PINMODE INPUT_PULLUP
  pinMode(A3, ADDR_PINMODE);
  pinMode(A2, ADDR_PINMODE);
  pinMode(A1, ADDR_PINMODE);
  pinMode(A0, ADDR_PINMODE);
  pinMode(2, OUTPUT);
  pinMode(3, OUTPUT);
  pinMode(4, OUTPUT);
  pinMode(5, OUTPUT);
  pinMode(6, OUTPUT);
  pinMode(7, OUTPUT);
  pinMode(8, OUTPUT);
  pinMode(9, OUTPUT);
  Serial.begin(9600);
}

uint8_t data = 0x00, data0 = 0x00;

void loop() {
  uint8_t addr;
  addr = (digitalRead(A3) << 3) | (digitalRead(A2) << 2) | (digitalRead(A1) << 1) | (digitalRead(A0));
  data = mem[addr];
  //Serial.print(addr, HEX); Serial.print(' '); Serial.println(data, HEX);
  if (data != data0){
    if (data & 0x01) digitalWrite(8, 1); else digitalWrite(8, 0);
    if (data & 0x02) digitalWrite(9, 1); else digitalWrite(9, 0);
    if (data & 0x04) digitalWrite(2, 1); else digitalWrite(2, 0);
    if (data & 0x08) digitalWrite(3, 1); else digitalWrite(3, 0);
    if (data & 0x10) digitalWrite(4, 1); else digitalWrite(4, 0);
    if (data & 0x20) digitalWrite(5, 1); else digitalWrite(5, 0);
    if (data & 0x40) digitalWrite(6, 1); else digitalWrite(6, 0);
    if (data & 0x80) digitalWrite(7, 1); else digitalWrite(7, 0);
    data0 = data;
  }
}

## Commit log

2024-02-27 fix filename
2024-02-28 add PCB data
2025-11-03 update for V2
2026-04-20 add PCB&tester FW
2026-04-22 add BOM&photo
